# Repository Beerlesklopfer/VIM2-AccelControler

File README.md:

# VIM2-AccelControler

A Matlab App and Arduino Firmware to demonstrate the Acceleration af a rotary mass

This paper explains the context and structure of an experiment on rotational acceleration and its moment of
its section modulus. The use of a stepper motor in the mechanical experimental apparatus and the connection via
connection via Arduino with custom firmware allows the control of all parameters via Modbus. The experiment can be
controlled by a widget-based Matlab app via GUI. Experimental data is automatically generated, recorded
recorded and visually processed for the user. The asynchronous Modbus communication between App
and controller could not be realized error-free within the scope of this project. Any errors that occurred were
analyzed in detail and solutions were developed.

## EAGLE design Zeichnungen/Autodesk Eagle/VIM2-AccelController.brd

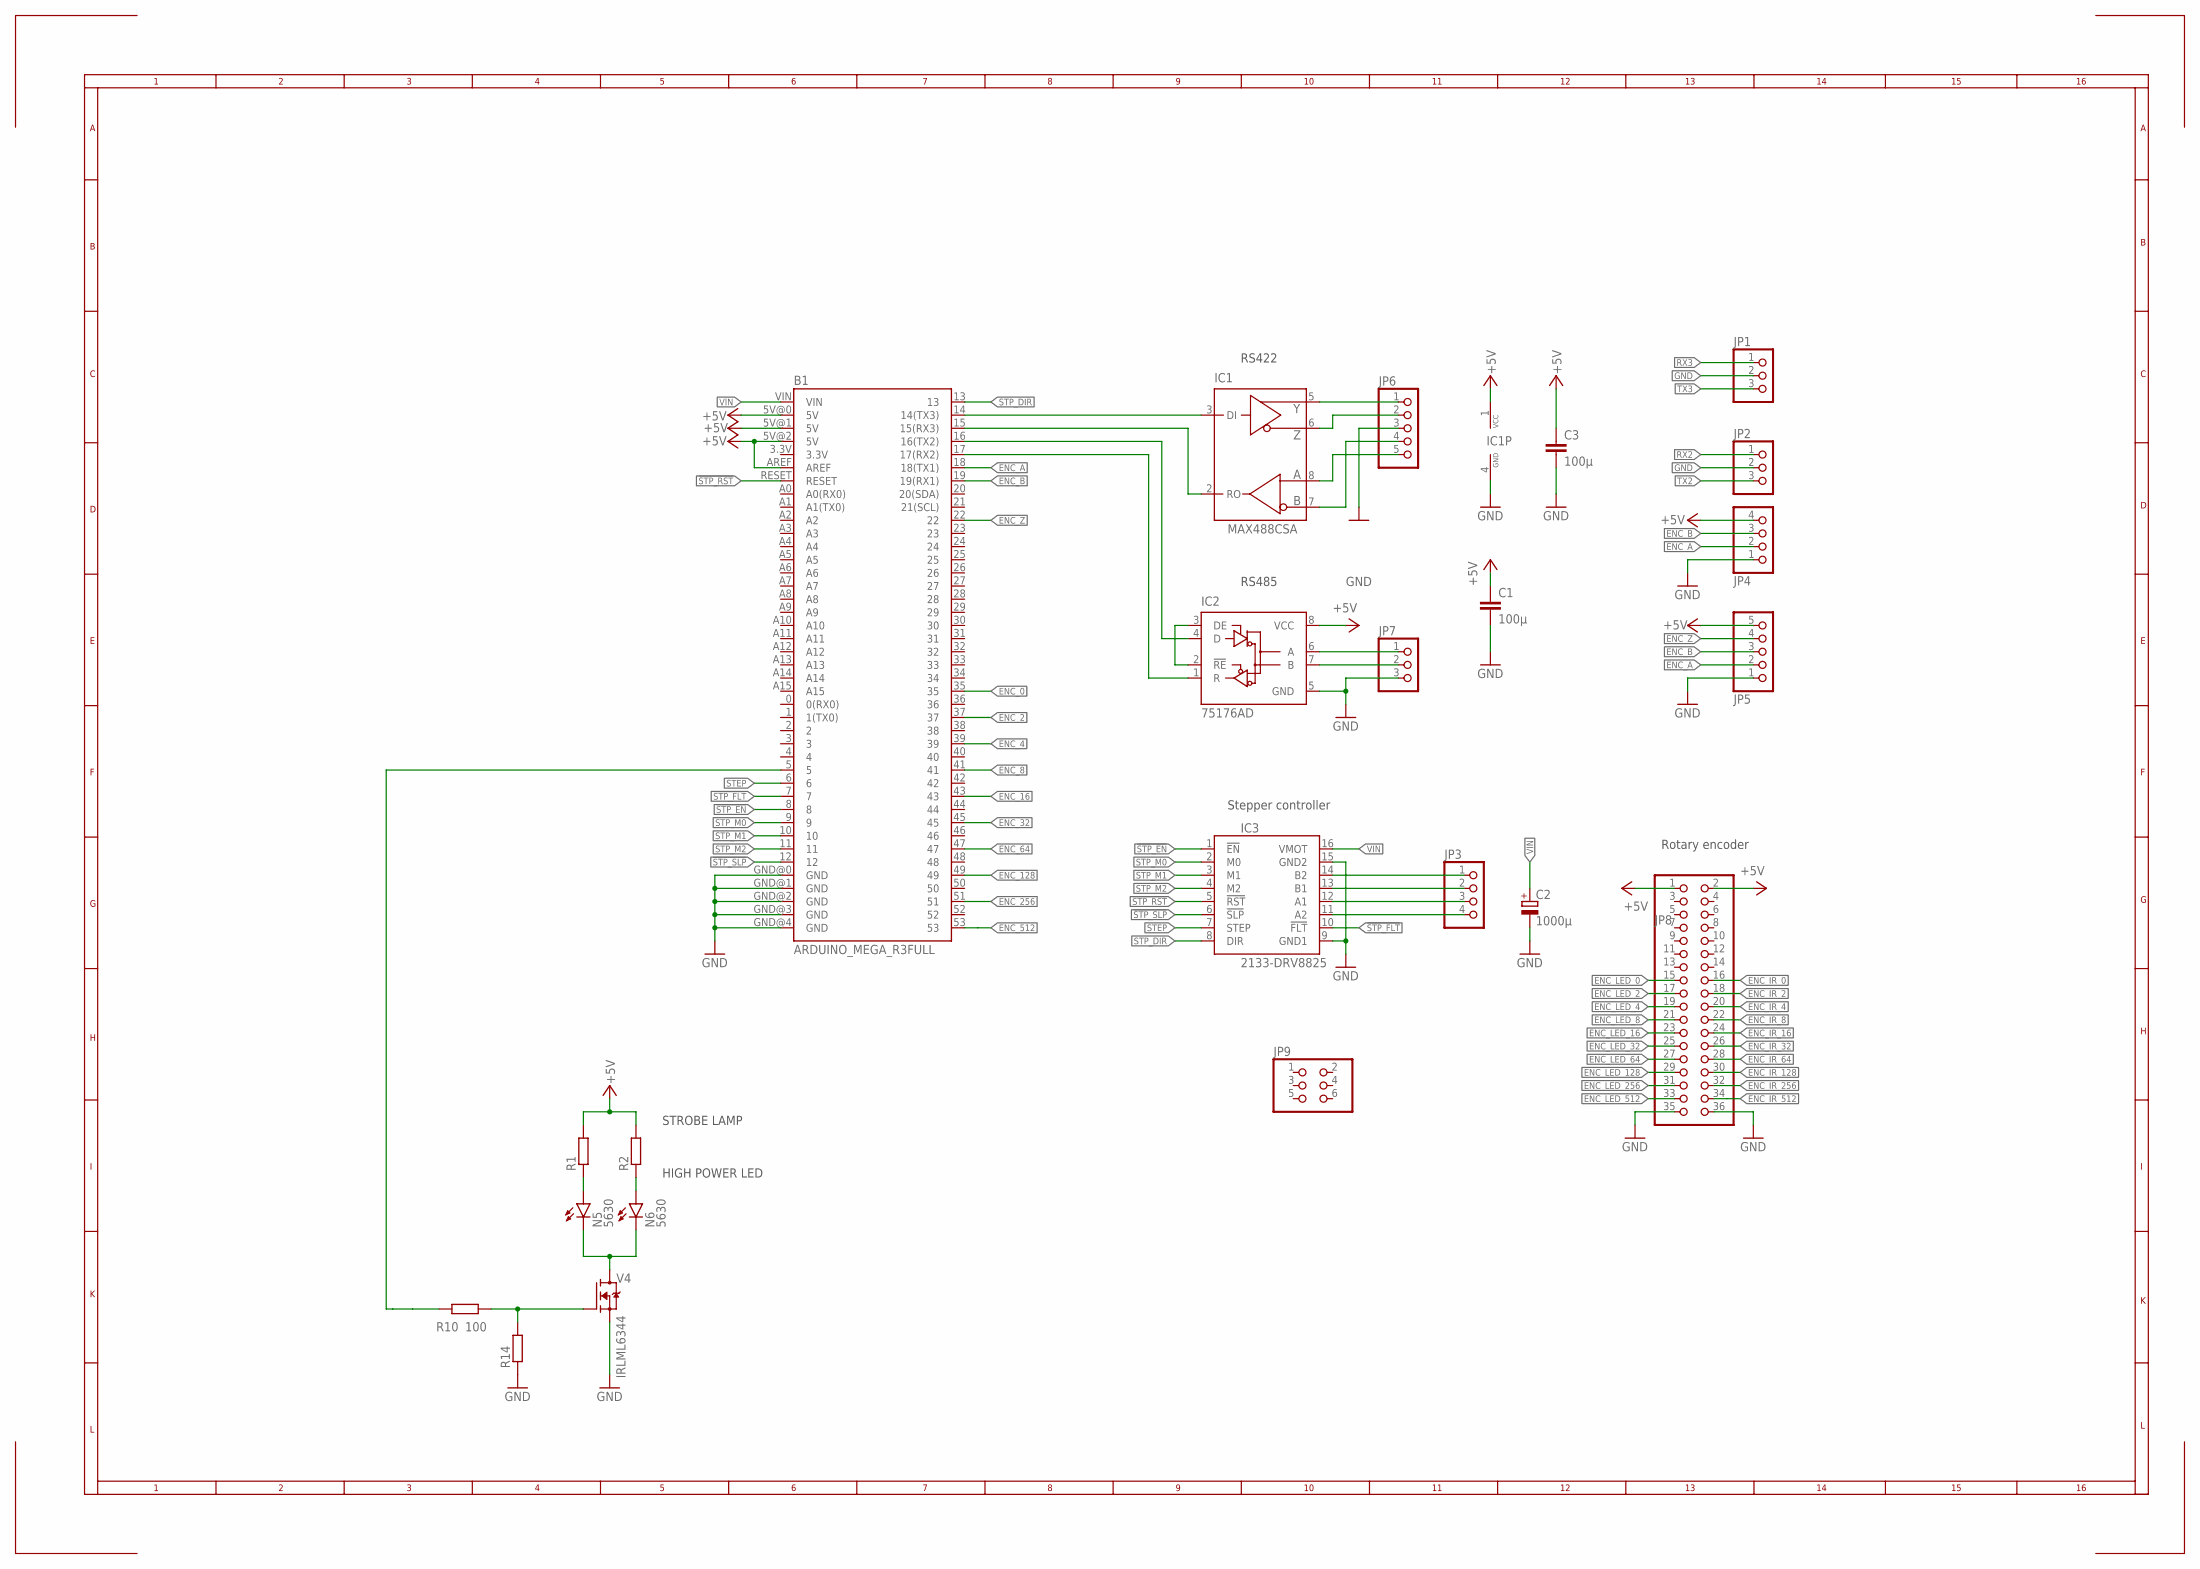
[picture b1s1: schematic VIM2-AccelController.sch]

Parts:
B1: ARDUINO_MEGA_R3FULL; ARDUINO_MEGA
C1, C3: 100µ; C0805K
C2: 1000µ; E5-8,5
IC1: MAX488CSA; SO08
IC2: 75176AD; D_R-PDSO-G8
IC3: 2133-DRV8825; DRV8825
JP1, JP2, JP7: PINHD-1X3; 1X03
JP3: PINHD-1X4/90; 1X04/90
JP4: PINHD-1X4; 1X04
JP5, JP6: PINHD-1X5; 1X05
JP8: PINHD-2X18; 2X18
JP9: PINHD-2X3; 2X03
N5, N6: 5630; 5730
R1, R2, R10: 100; R0805
R14: 4k7; R0805
V4: IRLML6344; SOT23

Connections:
!STP_EN: B1.8, IC3.1 (!EN)
!STP_FLT: B1.7, IC3.10 (!FLT)
!STP_RST: B1.RESET, IC3.5 (!RST)
!STP_SLP: B1.12, IC3.6 (!SLP)
+5V: B1.5V@0 (5V), B1.5V@1 (5V), B1.5V@2 (5V), B1.AREF, C1.1, C3.1, IC1.1 (VCC), IC2.8 (VCC), JP4.4, JP5.5, JP8.1, JP8.2, R1.2, R2.2
A: IC1.8 (A), JP6.5
B: IC1.7 (B), JP6.4
ENC_0: B1.35
ENC_2: B1.37
ENC_4: B1.39
ENC_8: B1.41
ENC_16: B1.43
ENC_32: B1.45
ENC_64: B1.47
ENC_128: B1.49
ENC_256: B1.51
ENC_512: B1.53
ENC_A: B1.18 (18(TX1)), JP4.2, JP5.2
ENC_B: B1.19 (19(RX1)), JP4.3, JP5.3
ENC_IR_0: JP8.16
ENC_IR_2: JP8.18
ENC_IR_4: JP8.20
ENC_IR_8: JP8.22
ENC_IR_16: JP8.24
ENC_IR_32: JP8.26
ENC_IR_64: JP8.28
ENC_IR_128: JP8.30
ENC_IR_256: JP8.32
ENC_IR_512: JP8.34
ENC_LED_0: JP8.15
ENC_LED_2: JP8.17
ENC_LED_4: JP8.19
ENC_LED_8: JP8.21
ENC_LED_16: JP8.23
ENC_LED_32: JP8.25
ENC_LED_64: JP8.27
ENC_LED_128: JP8.29
ENC_LED_256: JP8.31
ENC_LED_512: JP8.33
ENC_Z: B1.22, JP5.4
GND: B1.GND@0 (GND), B1.GND@1 (GND), B1.GND@2 (GND), B1.GND@3 (GND), B1.GND@4 (GND), C1.2, C2.-, C3.2, IC1.4 (GND), IC2.5 (GND), IC3.9 (GND1), IC3.15 (GND2), JP1.2, JP2.2, JP4.1, JP5.1, JP6.3, JP7.3, JP8.35, JP8.36, R14.1, V4.2 (S)
unnamed: N5.P$1 (A), N5.P$2 (A), R1.1
unnamed: IC2.2 (!RE), IC2.3 (DE)
unnamed: N5.P$3 (C), N6.P$3 (C), V4.3 (D)
unnamed: R10.1, R14.2, V4.1 (G)
unnamed: IC2.6 (A), JP7.1
unnamed: IC2.7 (B), JP7.2
unnamed: IC3.14 (B2), JP3.1
unnamed: IC3.13 (B1), JP3.2
unnamed: IC3.12 (A1), JP3.3
unnamed: IC3.11 (A2), JP3.4
unnamed: N6.P$1 (A), N6.P$2 (A), R2.1
RX2: B1.17 (17(RX2)), IC2.1 (R), JP2.1
RX3: B1.15 (15(RX3)), IC1.2 (RO), JP1.1
STEP: B1.6, IC3.7 (STEP)
STP_DIR: B1.13, IC3.8 (DIR)
STP_M0: B1.9, IC3.2 (M0)
STP_M1: B1.10, IC3.3 (M1)
STP_M2: B1.11, IC3.4 (M2)
TX2: B1.16 (16(TX2)), IC2.4 (D), JP2.3
TX3: B1.14 (14(TX3)), IC1.3 (DI), JP1.3
VIN: B1.VIN, C2.+, IC3.16 (VMOT)
WH: B1.5, R10.2
Y: IC1.5 (Y), JP6.1
Z: IC1.6 (Z), JP6.2

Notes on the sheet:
STROBE LAMP
HIGH POWER LED
Stepper controller
Rotary encoder
RS422
RS485

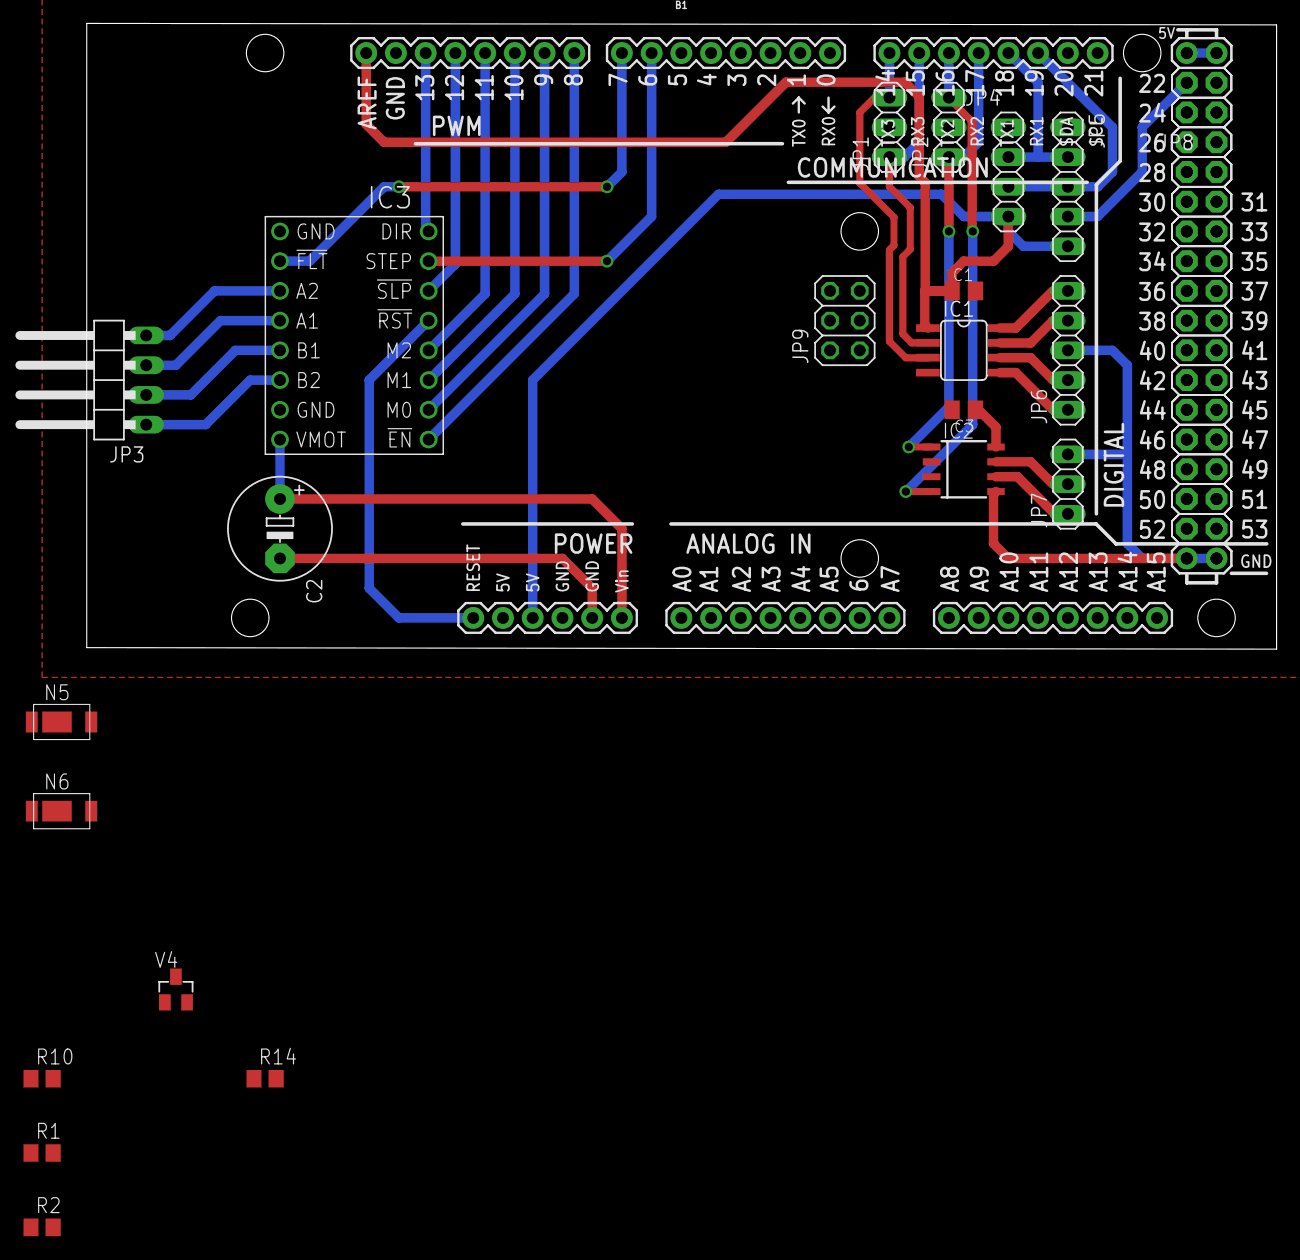
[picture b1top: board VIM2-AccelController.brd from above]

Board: 2 copper layers, 101.7 x 53.5 mm, 23 parts (0 on the bottom side), 35 nets.

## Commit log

2022-02-28 First TEST Release
2022-02-28 minor changes
2022-02-28 Translated
2022-02-28 Added Datasheed LPD3806-400BM-G5-24C
2022-02-28 Added EAGLE as PDF
2022-02-28 Added Timer4
2022-02-28 Update README.md
    Minor changes; sadly Modbus Slave emmulator fromSourceforge only supports MB Addresses above 100k

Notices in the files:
parts and their libraries:
SparkFun-Boards: Licensing: Creative Commons ShareAlike 4.0 International - https://creativecommons.org/licenses/by-sa/4.0
